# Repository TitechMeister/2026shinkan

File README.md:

# Device-ATmega88_Board

Meister新歓2025の作業体験に使う基板です。

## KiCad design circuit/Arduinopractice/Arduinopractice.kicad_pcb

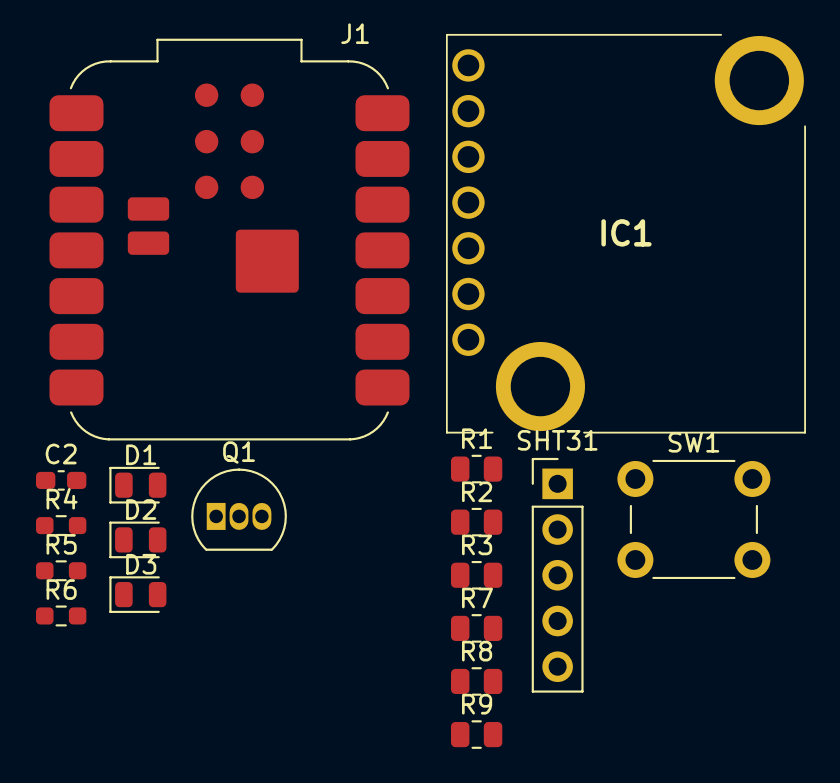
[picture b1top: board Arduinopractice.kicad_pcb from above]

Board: 2 copper layers, 18 parts (0 on the bottom side), 16 nets, no tracks yet.

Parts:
C2: 0.1u; C_0603_1608Metric_Pad1.08x0.95mm_HandSolder
D1, D2, D3: LED; LED_0805_2012Metric
IC1: MB1010-000; MB1010000
J1: XIAORP2040; MCU_Seeed_ESP32C3
Q1: 2SC1815; TO-92_Inline
R1, R2, R3: 330; R_0805_2012Metric
R4: 1k; R_0603_1608Metric_Pad0.98x0.95mm_HandSolder
R5, R6: 10k; R_0603_1608Metric_Pad0.98x0.95mm_HandSolder
R7: 10k; R_0805_2012Metric
R8, R9: 4.7k; R_0805_2012Metric
SHT31: Conn_01x05_Socket; PinHeader_1x05_P2.54mm_Vertical
SW1: SW_Push_Dual; SW_PUSH_6mm_H4.3mm

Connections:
+3V3: C2.1, IC1.6 (+5), J1.12, R4.2, R7.2, R8.2, R9.1, SHT31.1
Analog: IC1.3 (AN), J1.4
GND: C2.2, IC1.1 (BW), IC1.7 (GND), J1.13, Q1.1 (E), R6.1, SHT31.5
unnamed: D1.2 (A), R1.2
unnamed: D2.2 (A), R2.2
unnamed: D3.2 (A), R3.2
unnamed: IC1.5 (TX), R5.2, R6.2
unnamed: J1.1, R1.1
unnamed: J1.2, R2.1
unnamed: J1.3, R3.1
unnamed: Q1.3 (B), R5.1
PWM: IC1.2 (PW), J1.9
RX: J1.8, Q1.2 (C), R4.1
SCL: J1.6, R8.1, SHT31.3
SDA: J1.5, R9.2, SHT31.2
SW: J1.10, R7.1, SW1.1

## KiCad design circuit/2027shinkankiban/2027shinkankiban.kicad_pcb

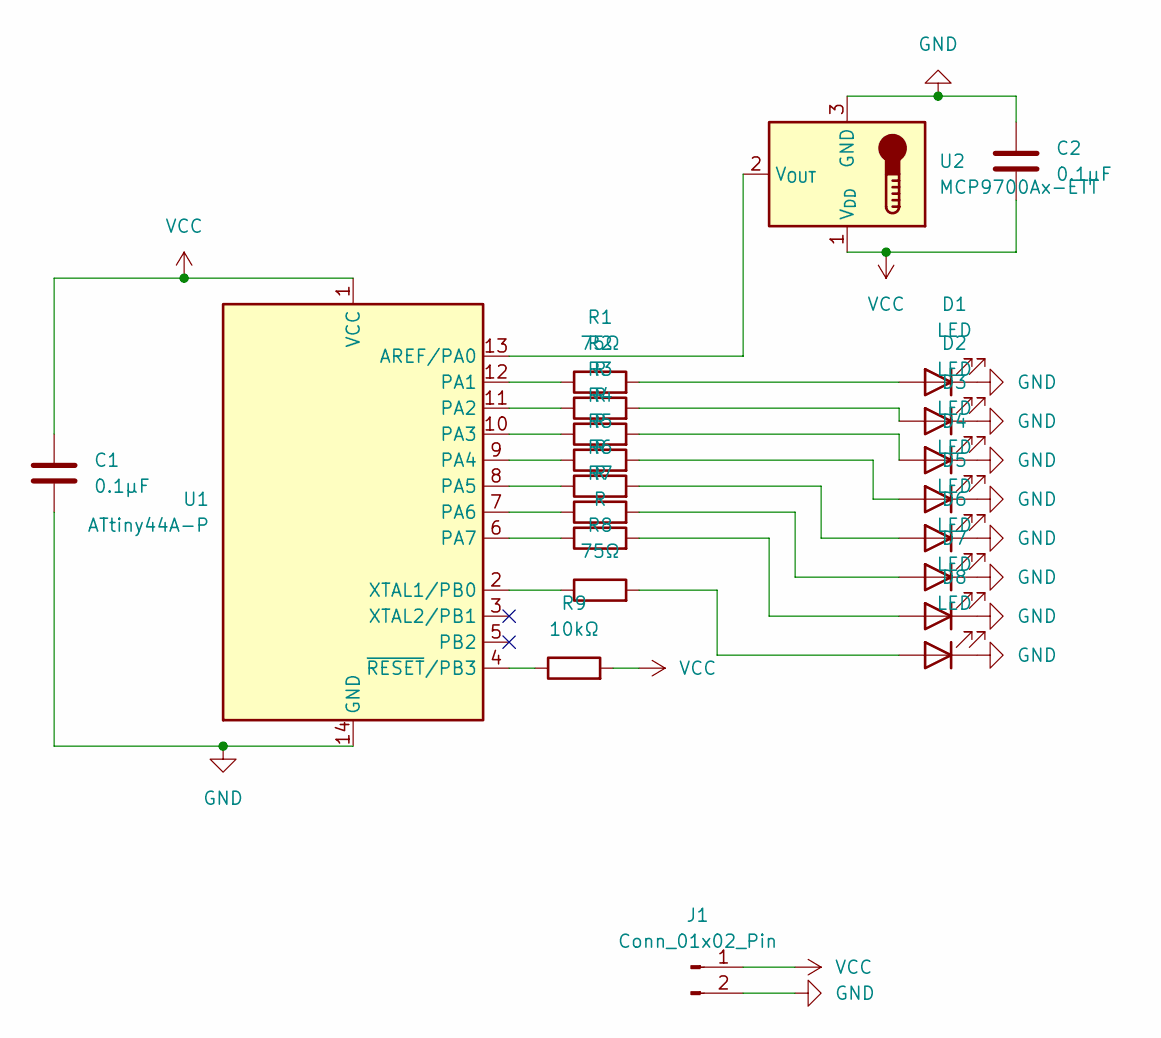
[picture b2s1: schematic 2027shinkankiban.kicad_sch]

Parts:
C1, C2: 0.1μF; C_Disc_D5.0mm_W2.5mm_P5.00mm
D1, D2, D3, D4, D5, D6, D7, D8: LED; LED_D5.0mm
J1: Conn_01x02_Pin; PinHeader_1x02_P2.54mm_Vertical
R1, R8: 75Ω; R_Axial_DIN0207_L6.3mm_D2.5mm_P10.16mm_Horizontal
R2, R3, R4, R5, R6, R7: R; R_Axial_DIN0207_L6.3mm_D2.5mm_P10.16mm_Horizontal
R9: 10kΩ; R_Axial_DIN0207_L6.3mm_D2.5mm_P10.16mm_Horizontal
U1: ATtiny44A-P; DIP-14_W7.62mm
U2: MCP9700Ax-ETT; SOT-23

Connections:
GND: C1.2, C2.1, D1.1 (K), D2.1 (K), D3.1 (K), D4.1 (K), D5.1 (K), D6.1 (K), D7.1 (K), D8.1 (K), J1.2, U1.14 (GND), U2.3 (GND)
unnamed: D1.2 (A), R1.2
unnamed: D2.2 (A), R2.2
unnamed: D3.2 (A), R3.2
unnamed: D4.2 (A), R4.2
unnamed: D5.2 (A), R5.2
unnamed: D6.2 (A), R6.2
unnamed: D7.2 (A), R7.2
unnamed: D8.2 (A), R8.2
unnamed: U1.13 (AREF/PA0), U2.2 (V_{OUT})
unnamed: R1.1, U1.12 (PA1)
unnamed: R2.1, U1.11 (PA2)
unnamed: R3.1, U1.10 (PA3)
unnamed: R4.1, U1.9 (PA4)
unnamed: R5.1, U1.8 (PA5)
unnamed: R6.1, U1.7 (PA6)
unnamed: R7.1, U1.6 (PA7)
unnamed: R8.1, U1.2 (XTAL1/PB0)
unnamed: R9.1, U1.4 (~RESET/PB3)
VCC: C1.1, C2.2, J1.1, R9.2, U1.1 (VCC), U2.1 (V_{DD})

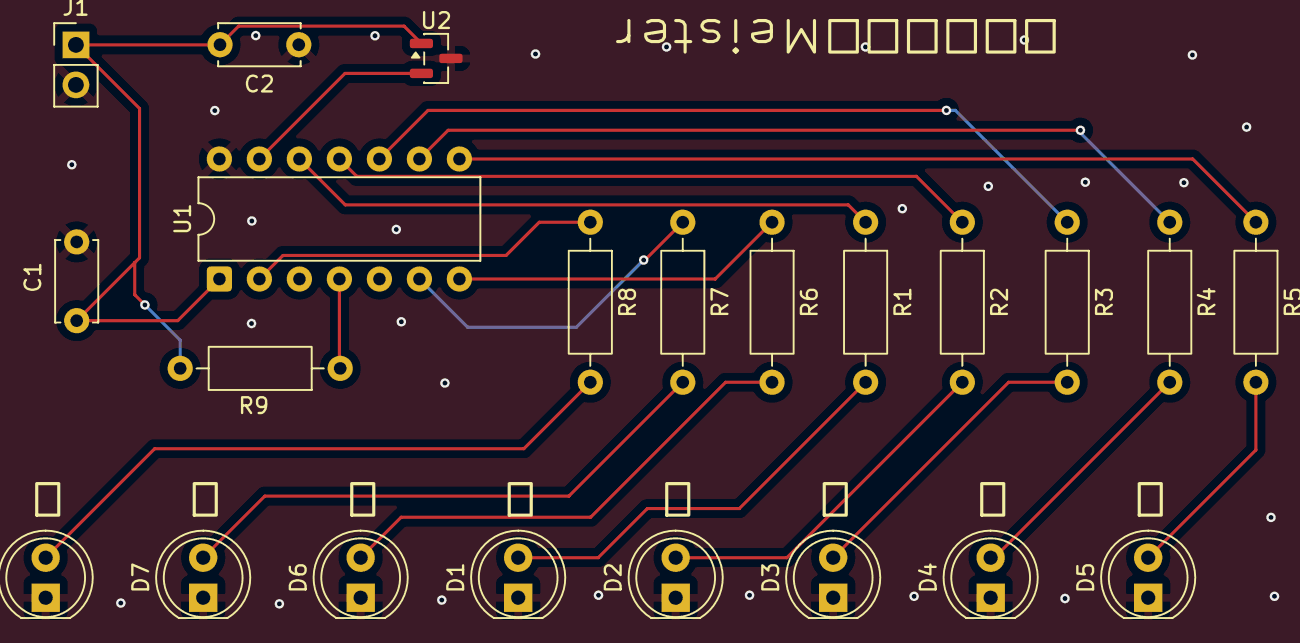
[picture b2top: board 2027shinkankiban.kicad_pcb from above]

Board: 2 copper layers, 22 parts (0 on the bottom side), 20 nets.

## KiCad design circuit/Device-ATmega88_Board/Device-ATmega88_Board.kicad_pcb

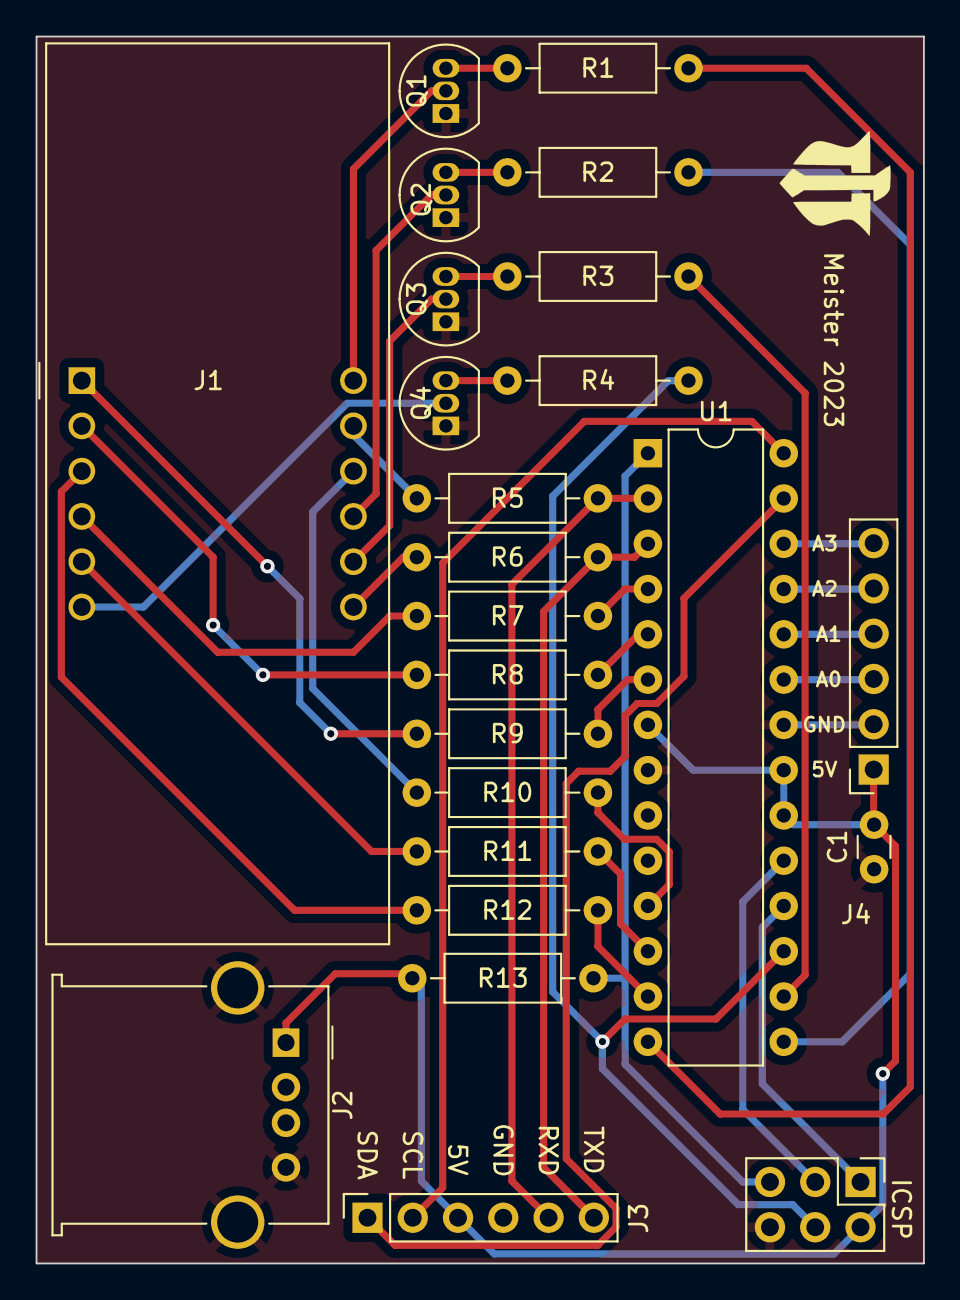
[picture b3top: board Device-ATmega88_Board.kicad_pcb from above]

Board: 2 copper layers, 49.8 x 68.8 mm, 24 parts (0 on the bottom side), 39 nets.

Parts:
C1: C; C_Disc_D3.0mm_W1.6mm_P2.50mm
J1: 7seg; CA56-12SRWA
J2: USB_A; USB_A_Molex_67643_Horizontal
J3, J4: Conn_01x06_Female; PinSocket_1x06_P2.54mm_Vertical
J5: ICSP; PinHeader_2x03_P2.54mm_Vertical
Q1, Q2, Q3, Q4: 2SC1815; TO-92_Inline
R1, R2, R3, R4, R5, R6, R7, R8, R9, R10, R11, R12, R13: 10k; R_Axial_DIN0207_L6.3mm_D2.5mm_P10.16mm_Horizontal
U1: ATmega328P-P; DIP-28_W7.62mm

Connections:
7SEG-A: J1.11, R5.2
7SEG-B: J1.7, R6.2
7SEG-C: J1.4, R7.2
7SEG-D: J1.2, R8.2
7SEG-D1: J1.12, Q1.2 (C)
7SEG-D2: J1.9, Q2.2 (C)
7SEG-D3: J1.8, Q3.2 (C)
7SEG-D4: J1.6, Q4.2 (C)
7SEG-DP: J1.3, R12.2
7SEG-E: J1.1, R9.2
7SEG-F: J1.10, R10.2
7SEG-G: J1.5, R11.2
+5V: C1.2, J2.1 (VBUS), J3.3, J4.1, J5.2, R13.2, U1.7 (VCC), U1.20 (AVCC), U1.21 (AREF)
AD0: J4.3, U1.23 (PC0)
AD1: J4.4, U1.24 (PC1)
AD2: J4.5, U1.25 (PC2)
AD3: J4.6, U1.26 (PC3)
GND: C1.1, J2.4 (GND), J2.5 (Shield), J3.4, J4.2, J5.6, Q1.1 (E), Q2.1 (E), Q3.1 (E), Q4.1 (E), U1.8 (GND), U1.22 (GND)
MISO: J5.1, U1.18 (PB4)
MOSI: J5.4, R4.1, U1.17 (PB3)
unnamed: Q1.3 (B), R1.2
unnamed: Q2.3 (B), R2.2
unnamed: Q3.3 (B), R3.2
unnamed: Q4.3 (B), R4.2
unnamed: R1.1, U1.14 (PB0)
unnamed: R2.1, U1.15 (PB1)
unnamed: R3.1, U1.16 (PB2)
unnamed: R7.1, U1.4 (PD2)
unnamed: R8.1, U1.5 (PD3)
unnamed: R9.1, U1.6 (PD4)
unnamed: R10.1, U1.11 (PD5)
unnamed: R11.1, U1.12 (PD6)
unnamed: R12.1, U1.13 (PD7)
RST: J5.5, R13.1, U1.1 (~RESET/PC6)
RXD: J3.5, R5.1, U1.2 (PD0)
SCK: J5.3, U1.19 (PB5)
SCL: J3.2, U1.28 (PC5)
SDA: J3.1, U1.27 (PC4)
TXD: J3.6, R6.1, U1.3 (PD1)

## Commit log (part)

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2025-04-06 24代の新勧のデータをコピーしました
2025-04-07 マークダウンをかきました
2025-04-07 URLの修正
2025-04-07 りーどみーの修正
2025-04-07 新勧サイトに飛べるように修正
2025-04-07 URLを微修正
2025-04-07 細部の修正
2025-04-07 びしゅうせい
2025-04-15 avrdudeのコマンド部分の修正
2025-04-17 プログラムを修正
2026-02-21 Add Meister-KiadLibrary as submodule
2026-02-22 2027年新歓用基板を追加
2026-04-24 やらかした
2026-04-24 Root commit: initialize empty branch
2026-04-25 フォルダなどを追加
2026-04-25 KiCadライブラリをサブモジュールとして追加
2026-04-25 いろいろ追加
2026-04-30 lesson5までを作成
2026-05-01 Lesson7まで作成
2026-05-03 Lesson10まで追加
2026-05-06 Lesson15のコードまで追加
2026-05-08 コードをすべて作成
2026-05-08 とりあえず完成
2026-05-29 シンボルを変更
2026-06-17 Lesson19まで追加
